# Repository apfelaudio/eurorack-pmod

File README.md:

# Eurorack PMOD

**Eurorack PMOD** is a [certified open hardware](https://certification.oshwa.org/de000135.html) Eurorack module that plugs directly into many FPGA boards, which makes it easy to combine the world of FPGAs and [hardware electronic music synthesis](https://en.wikipedia.org/wiki/Eurorack). The latest (R3.3) hardware looks like this:

## How does it work? ([tutorial video](https://youtu.be/TcqFej9GK8U))
- Plug eurorack-pmod into an FPGA development board of your choice. Here is a list of [boards already supported by the examples](gateware/boards).
- Get started with some [example DSP cores](gateware/cores). Examples include calibration, sampling, effects, synthesis sources and so on. The design files can be synthesized to a bitstream using Yosys' [oss-cad-suite](https://github.com/YosysHQ/oss-cad-suite-build).

## :notes: Project Showcase :sparkles:

- **[FPGA-based neural-net waveshaper](https://matpalm.com/blog/wavenet_on_fpga/)** - (from [matpalm@](https://github.com/matpalm))
- **[Teensy 4.x I2S TDM w/ Eurorack PMOD](https://github.com/Lytrix/Teensy4-i2s-TDM)** - (from [lytrix@](https://github.com/Lytrix))
- **[8-channel USB2 soundcard](https://github.com/apfaudio/eurorack-pmod-usb-soundcard)** - mostly in Amaranth.
- **[Daisy Seed TDM for Eurorack PMOD](https://github.com/heartwerker/daisy_seed_tdm_eurorack_pmod)** - (from [heartwerker@](https://github.com/heartwerker))
- **[`apu_chord` core](https://github.com/proppy/eurorack-pmod/tree/apu_chord)** - (from [proppy@](https://github.com/proppy))
- **[Real-time DSP with Rust on LiteX](https://github.com/apfaudio/eurorack-pmod-litex)** - mostly in Rust/Migen.

# R3.3 hardware details

- 3HP module compatible with modular synthesizer systems.
    - Module depth is 35mm with both ribbon cables attached.
- [PMOD](https://en.wikipedia.org/wiki/Pmod_Interface) connector compatible with many FPGA development boards.
- 8 (4 in + 4 out) DC-coupled audio channels, 192KHz / 32bit sampling supported.
- PWM-controlled, user-programmable red/green LEDs on each output channel.
- Jack insertion detection on input & output jacks.
- Calibration EEPROM for unique ID and storing calibration data.
- [new!] Touch and proximity sensing on all unused jacks as an extra input method.
    - See the `gateware/cores/touch_cv.sv` core for an example of how to use this.

**Compared to R3.1, the changes across R3.2 and R3.3 [are summarized here](https://github.com/apfaudio/eurorack-pmod/issues/50)**

[Want one?](#manufacturing). More photos can be found [below](#photos).

## Included examples
This repository contains a bunch of example DSP cores which are continuously being updated:
- `gateware/cores/pitch_shift.sv` - Pitch shifter
- `gateware/cores/filter.sv` - Filter (low pass + resonance)
- `gateware/cores/touch_cv.sv` - Touch sensing to CV converter
- `gateware/cores/clkdiv.sv` - Clock divider
- `gateware/cores/sampler.sv` - .wav sampler
- `gateware/cores/seqswitch.sv` - Sequential routing switch
- `gateware/cores/digital_echo.sv` - Echo / delay effect
- `gateware/cores/vca.sv` - VCA (voltage controlled amplifier)
- `gateware/cores/vco.sv` - VCO (voltage controlled oscillator)
- `gateware/cores/bitcrush.sv` - Bitcrusher

These examples can all run out of the box on the development boards listed below.

## Choosing an FPGA development board
An FPGA development board itself is NOT included! Essentially anything iCE40 or ECP5 based that has a PMOD connector will support the open-source tools and the examples in this project. Just make sure you have enough LUTS, >3K is enough to do interesting things.

The following development boards have been tested with `eurorack-pmod` and are supported by the examples in the github repository
- iCEbreaker (iCE40 based)
- [iCESugar](https://github.com/wuxx/icesugar) (iCE40 based, iCE40UP5K version)
- ECPIX-5 (ECP5 based)
- Colorlight i5 (ECP5 based)
- Colorlight i9 (ECP5 based)
- pico-ice from TinyVision (iCE40 based)
- CCGM1A1 Gatemate EVB from CologneChip - [**experimental!** see here](gateware/boards/gatemate_evb/README.md)

## PMOD Pinout

The PMOD pinout is on the silkscreen on the back side of the board. Details are below. Note that Pin 1 is the SQUARE pad.

1) SDI (AK4619VN SDIN1)
2) SCL (I2C SCL for AK4619VN CODEC, EEPROM, LED + JACK IO expanders)
3) SDO (AK4619VN SDOUT1)
4) SDA (I2C SDA)
5) LRCK (CODEC clock line)
6) PDN (CODEC power down, also connected to LED output enable and JACK reset line -- HIGH means everything is on)
7) BICK (CODEC clock line)
8) MCLK (CODEC clock line)
9) GND
10) GND
11) 3V3 IN
12) 3V3 IN

## Getting Started

I have tested builds on Linux, Mac and Windows (under MSYS2). All are tested in CI.

0. Install the [OSS FPGA CAD flow](https://github.com/yosyshq/oss-cad-suite-build).
    - You may be able to get yosys / verilator from other package managers but I recommend using the [releases from YosysHQ](https://github.com/yosyshq/oss-cad-suite-build) so you're using the same binaries that CI is using.
    - On Linux, once the YosysHQ suite is installed and in PATH, you should be able to just use `make` in the gateware directory.
    - On Windows, CI is using MSYS2 with MINGW64 shell. Install MSYS2, MINGW64, extract the oss-cad-suite from YosysHQ and add it to PATH. Then you should be able to use `make` in the gateware directory.
    - Note: The gateware is automatically built and tested in CI, so for either platform it may be helpful to look at [`.github/workflows/main.yml`](.github/workflows/main.yml).

1. Build or obtain `eurorack-pmod` hardware and connect it to your FPGA development board using a ribbon cable or similar. (Double check that the pin mappings are correct, some ribbon cables will swap them on you! Default pinmaps are for the ribbon cables I shipped with hardware, you need to flip the pinmaps for a direct connection PMOD -> FPGA)
2. Try some of the examples. From the `gateware` directory, type `make` to see valid commands. By default if you do not select a CORE it will compile a bitstream with the 'mirror' core, which just sends inputs to outputs. Note, you'll need to run `git submodule update --init --recursive` from the repo root after checkout.
2. Calibrate your hardware using the process described in [`gateware/cal/cal.py`](gateware/cal/cal.py). Use this to create your own `gateware/cal/cal_mem.hex` to compensate for any DC biases in the ADCs/DACs. (this step is only necessary if you need sub-50mV accuracy on your inputs/outputs, which is the case if you are tuning oscillators, not so much if you are creating rhythm pulses.

# Project structure
The project is split into 2 directories, [`hardware`](hardware) for the PCB/panel and [`gateware`](gateware) for the FPGA source. Some interesting directories:
- [`gateware/cores`](gateware/cores): example user core implementations (i.e sequential switch, bitcrusher, filter, vco, vca, sampler etc).
- [`gateware/top.sv`](gateware/top.sv): top-level gateware with defines for selecting features.
- [`gateware/cal/cal.py`](gateware/cal/cal.py): tool used to calibrate the hardware after assembly, generating calibration memory.
- [`gateware/drivers`](gateware/drivers): driver for CODEC and I2C devices used on this board.
- [`hardware/eurorack-pmod-r3`](hardware/eurorack-pmod-r3): KiCAD design files for PCB and front panel.
- [`hardware/fab`](hardware/fab): gerber files and BOM for manufacturing the hardware.

# Manufacturing

# R3.1 Hardware (no longer manufactured)

The above README focuses on R3.3, which is currently being manufactured.

Revision R3.1 was sold out in 2023. It's no longer manufactured, however this repository still supports it if you use the `HW_REV=HW_R31` flag when building. I left some of the old photos here in case they are useful.

From the gateware perspective, there is almost no difference between R3.1 and R3.3 and so any cores should be compatible with both (unless they use new features of R3.3 e.g. touch sensitive jacks).

## R3.1 boards

## R3.1 hardware details

## R3.1 technical

- 3HP module compatible with modular synthesizer systems.
    - Module depth is 47mm with both ribbon cables attached
    - This fits nicely in e.g. a 4MS POD 48X (pictured below).
- PMOD connector compatible with most FPGA development boards.
- 8 (4 in + 4 out) DC-coupled audio channels, 192KHz / 32bit sampling supported.
- PWM-controlled, user-programmable red/green LEDs on each output channel.
- Jack insertion detection on input & output jacks.
- Calibration EEPROM for unique ID and storing calibration data.
- I/O is about +/- 8V capable, wider is possible with a resistor change.

## Known limitations
- Moved to github issues

# Photos

## `eurorack-pmod` R3.1 connected to iCEBreaker

# License

Hardware and gateware are released under the CERN Open-Hardware License V2 `CERN-OHL-S`, mirrored in the LICENSE text in this repository.

If you wish to license parts of this design in a commercial product without a reciprocal open-source license, or you have a ground-breaking idea for a module we could work on together, feel free to contact me directly. See sebholzapfel.com.

*Copyright (C) 2022-2024 Sebastian Holzapfel*

The above LICENSE and copyright notice does NOT apply to imported artifacts in this repository (i.e datasheets, third-party footprints).

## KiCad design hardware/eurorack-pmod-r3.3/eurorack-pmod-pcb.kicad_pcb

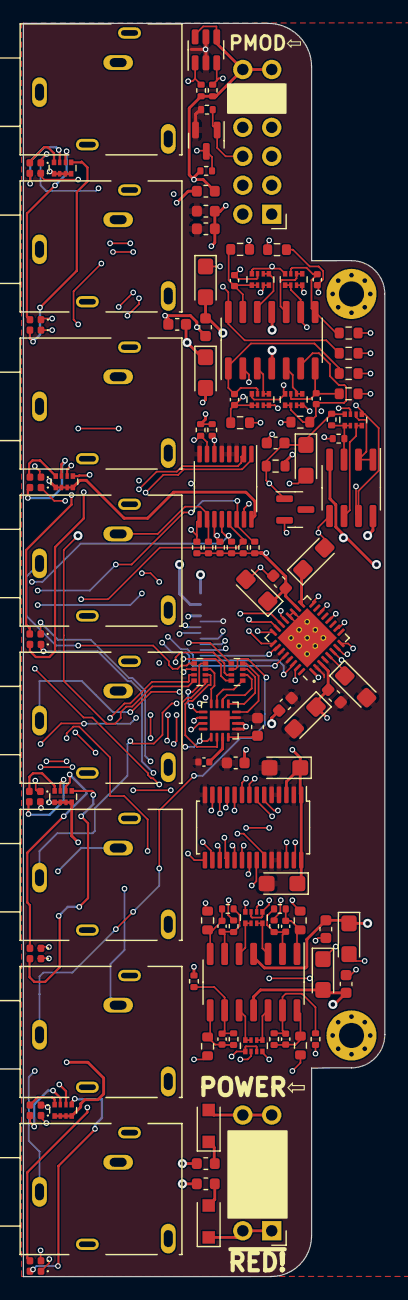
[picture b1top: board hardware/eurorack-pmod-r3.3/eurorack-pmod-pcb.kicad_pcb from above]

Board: 4 copper layers, 31.7 x 110.0 mm, 122 parts (1 on the bottom side), 124 nets.

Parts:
C2, C6, C8, C13, C14, C15, C17, C27, C29, C31: 100nF; C_0603_1608Metric
C3, C10, C16, C28: 100.0uF; CP_EIA-3216-10_Kemet-I
C4, C5, C9, C11, C26: 22.0uF; CP_EIA-3216-10_Kemet-I
C7, C12: 2.2uF; CP_EIA-3216-10_Kemet-I
C18, C19, C20, C21: 220pF; C_0402_1005Metric
C22, C23, C24, C25: 56p; C_0402_1005Metric
C30: 2.2nF; C_0402_1005Metric
D1, D2: 1N4007FL; D_SOD-123F
D3, D5, D7, D9, D11, D13, D15, D17: LED 0402 GREEN; LED_0402_1005Metric
D4, D6, D8, D10, D12, D14, D16, D18: LED 0402 RED; LED_0402_1005Metric
J1: CONN 2x5 P=2.54mm; PinHeader_2x05_P2.54mm_Horizontal
J2: CONN 2x6 P=2.54mm; PinHeader_2x06_P2.54mm_Horizontal
J3: Conn_01x14_Socket; FFC_0.5-14P_CTXJ-H2.0_1
J4, J5, J6, J7, J8, J9, J10, J11: AUDIO JACK PJ-324M0; pj324m
L1, L2, L3, L4, L5: FERRITE; L_0603_1608Metric
Q1: 2N7002E; SOT-23
R1, R2, R3, R4, R5, R8, R11, R14, R17, R20, R21, R24, R25, R28, R29, R32: 4K7; R_0402_1005Metric
R6, R9, R12, R15: 100K; R_0603_1608Metric
R7, R10, R13, R16, R18, R22, R26, R30: 1K; R_0603_1608Metric
R19, R23, R27, R31: 56K; R_0402_1005Metric
R33: 330R; R_0603_1608Metric
R42: X.X; R_0402_1005Metric
R43: 402K; R_0402_1005Metric
RN1, RN2, RN3, RN4: 14.3K; R_Array_Convex_4x0402
RN5, RN6, RN7: 100K; R_Array_Convex_4x0402
RN8, RN9, RN10, RN11: 120R; R_Array_Convex_4x0402
RN12, RN13: 560R; R_Array_Convex_4x0402
U1: AK4619VN AUDIO CODEC; QFN-32-1EP_5x5mm_P0.5mm_EP3.7x3.7mm_ThermalVias
U2, U3: TL074 OP AMP; SOIC-14_3.9x8.7mm_P1.27mm
U4: PCA9557PW IO EXPANDER; TSSOP-16_4.4x5mm_P0.65mm
U5: 24AA025UIDT EEPROM; SOT-23-6
U6: CY8CMBR3108; QFN-16-1EP_3x3mm_P0.5mm_EP1.75x1.75mm
U8: LM4040DBZ-3 VREF; SOT-23
U9: TL072 OP AMP; SOIC-8_3.9x4.9mm_P1.27mm
U10: PCA9635 LED DRIVER; TSSOP-28_4.4x9.7mm_P0.65mm

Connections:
+3.3VA: C10.1, C14.1, L4.1, R5.2, R8.2, R11.2, R14.2, R17.2, R21.2, R25.2, R29.2, R33.2, U1.18 (AVDD)
+12V: C5.1, C8.1, C11.1, C15.1, J3.3, L1.1, U2.4 (V+), U3.4 (V+), U9.8 (V+)
-12V: C4.2, C6.2, C9.2, C13.2, J3.1, L2.1, U2.11 (V-), U3.11 (V-), U9.4 (V-)
/-VCOM: RN1.8 (R1.2), RN2.8 (R1.2), RN3.8 (R1.2), RN4.8 (R1.2), RN5.1 (R1.1), RN5.3 (R3.1), RN6.1 (R1.1), RN6.3 (R3.1), RN7.5 (R4.2), U9.7
/BICK: J2.7, J3.10, U1.7 (BICK)
/CAP_SENSE_IN1: J4.G, RN12.8 (R1.2)
/CAP_SENSE_IN2: J5.G, RN12.7 (R2.2)
/CAP_SENSE_IN3: J6.G, RN12.6 (R3.2)
/CAP_SENSE_IN4: J7.G, RN12.5 (R4.2)
/CAP_SENSE_OUT1: J8.G, RN13.8 (R1.2)
/CAP_SENSE_OUT2: J9.G, RN13.7 (R2.2)
/CAP_SENSE_OUT3: J10.G, RN13.6 (R3.2)
/CAP_SENSE_OUT4: J11.G, RN13.5 (R4.2)
/JACK_DETECT_IN1: J4.SN, R5.1, U4.6 (IO0)
/JACK_DETECT_IN2: J5.SN, R8.1, U4.7 (IO1)
/JACK_DETECT_IN3: J6.SN, R11.1, U4.9 (IO2)
/JACK_DETECT_IN4: J7.SN, R14.1, U4.10 (IO3)
/JACK_DETECT_OUT1: J8.SN, R17.1, U4.11 (IO4)
/JACK_DETECT_OUT2: J9.SN, R21.1, U4.12 (IO5)
/JACK_DETECT_OUT3: J10.SN, R25.1, U4.13 (IO6)
/JACK_DETECT_OUT4: J11.SN, R29.1, U4.14 (IO7)
/LRCK: J2.5, J3.9, U1.6 (LRCK)
/MCLK: J2.8, J3.11, U1.8 (MCLK)
/PDN: J2.6, J3.12, Q1.1 (G), R4.2, U1.26 (PDN), U4.15 (~RESET)
/SCL: J2.2, J3.14, R1.1, U1.28 (SCL/SCLK), U4.1 (SCL), U5.1 (SCL), U6.15 (SCL), U10.26 (SCL)
/SDA: J2.4, J3.13, R2.1, U1.30 (SDA/SO), U4.2 (SDA), U5.3 (SDA), U6.14 (SDA), U10.27 (SDA)
/SDIN1: J2.1, J3.7, U1.1 (SDIN1)
/SDOUT1: J2.3, J3.8, U1.31 (SDOUT1)
/dual_mono_inputs1/IN1_3V: R7.2, U1.16 (IN1P/AIN1L/AIN3L)
/dual_mono_inputs1/IN2_3V: R10.2, U1.14 (IN2P/AIN1R/AIN3R)
/dual_mono_inputs2/IN1_3V: R13.2, U1.12 (IN3P/AIN4L/AIN6L)
/dual_mono_inputs2/IN2_3V: R16.2, U1.10 (IN4P/AIN4R/AIN6R)
/dual_mono_outputs1/OUT1: RN5.2 (R2.1), U1.22 (AOUT1L)
/dual_mono_outputs1/OUT2: RN5.4 (R4.1), U1.23 (AOUT1R)
/dual_mono_outputs2/OUT1: RN6.2 (R2.1), U1.24 (AOUT2L)
/dual_mono_outputs2/OUT2: RN6.4 (R4.1), U1.25 (AOUT2R)
/vref/+3V0_AREF: C26.1, C27.1, R33.1, R43.2, RN7.8 (R1.2), U1.21 (VREFH), U8.1 (K)
/~PDN: Q1.3 (D), R3.1, U10.23 (~OE)
GND: C4.1, C5.2, C6.1, C8.2, C9.1, C10.2, C11.2, C12.2, C13.1, C14.2, C15.2, C26.2, C27.2, J1.3, J1.4, J1.5, J1.6, J1.7, J1.8, J3.4, J4.S, J4.TN, J5.S, J5.TN, J6.S, J6.TN, J7.S, J7.TN, J8.S, J8.TN, J9.S, J9.TN, J10.S, J10.TN, J11.S, J11.TN, L3.1, L5.1, R20.1, R24.1, R28.1, R32.1, R42.1, RN1.3 (R3.1), RN1.4 (R4.1), RN2.3 (R3.1), RN2.4 (R4.1), RN3.3 (R3.1), RN3.4 (R4.1), RN4.3 (R3.1), RN4.4 (R4.1), RN7.7 (R2.2), U1.19 (VSS1), U1.20 (VREFL), U1.33 (PAD), U8.2 (A), U9.5 (+)
GNDD: C2.2, C3.2, C7.2, C16.2, C17.2, C28.2, C29.2, C30.2, C31.2, J2.9, J2.10, J3.6, L3.2, L5.2, Q1.2 (S), R4.1, U1.2 (SDIN2), U1.4 (VSS2), U1.27 (CAD/~CS), U1.29 (SI), U4.3 (A0), U4.4 (A1), U4.5 (A2), U4.8 (VSS), U5.2 (V_{SS}), U5.5 (WP), U6.7 (VSS), U6.17 (EP), U10.2 (A1), U10.4 (A3), U10.5 (A4), U10.14 (VSS), U10.24 (A5), U10.25 (A6)
unnamed: C22.2, R18.1, R19.1, U2.1
unnamed: C23.2, R22.1, R23.1, U2.7
unnamed: C24.2, R26.1, R27.1, U2.8
unnamed: C25.2, R30.1, R31.1, U2.14
unnamed: D1.2 (A), J1.9, J1.10
unnamed: D1.1 (K), L1.2
unnamed: D2.2 (A), L2.2
unnamed: D2.1 (K), J1.1, J1.2
unnamed: D3.2 (A), RN8.8 (R1.2)
unnamed: D3.1 (K), U10.6 (LED0)
unnamed: D4.2 (A), RN8.7 (R2.2)
unnamed: D4.1 (K), U10.7 (LED1)
unnamed: D5.2 (A), RN8.6 (R3.2)
unnamed: D5.1 (K), U10.8 (LED2)
unnamed: D6.2 (A), RN8.5 (R4.2)
unnamed: D6.1 (K), U10.9 (LED3)
unnamed: D7.2 (A), RN9.8 (R1.2)
unnamed: D7.1 (K), U10.10 (LED4)
unnamed: D8.2 (A), RN9.7 (R2.2)
unnamed: D8.1 (K), U10.11 (LED5)
unnamed: D9.2 (A), RN9.6 (R3.2)
unnamed: D9.1 (K), U10.12 (LED6)
unnamed: D10.2 (A), RN9.5 (R4.2)
unnamed: D10.1 (K), U10.13 (LED7)
unnamed: D11.2 (A), RN10.8 (R1.2)
unnamed: D11.1 (K), U10.15 (LED8)
unnamed: D12.2 (A), RN10.7 (R2.2)
unnamed: D12.1 (K), U10.16 (LED9)
unnamed: D13.2 (A), RN10.6 (R3.2)
unnamed: D13.1 (K), U10.17 (LED10)
unnamed: D14.2 (A), RN10.5 (R4.2)
unnamed: D14.1 (K), U10.18 (LED11)
unnamed: D15.2 (A), RN11.8 (R1.2)
unnamed: D15.1 (K), U10.19 (LED12)
unnamed: D16.2 (A), RN11.7 (R2.2)
unnamed: D16.1 (K), U10.20 (LED13)
unnamed: D17.2 (A), RN11.6 (R3.2)
unnamed: D17.1 (K), U10.21 (LED14)
unnamed: D18.2 (A), RN11.5 (R4.2)
unnamed: D18.1 (K), U10.22 (LED15)
unnamed: J4.T, R6.1
unnamed: J5.T, R9.1
unnamed: J6.T, R12.1
unnamed: J7.T, R15.1
unnamed: J8.T, R18.2
unnamed: J9.T, R22.2
unnamed: J10.T, R26.2
unnamed: J11.T, R30.2
unnamed: C18.1, R6.2, RN1.1 (R1.1), RN1.2 (R2.1), U3.2 (-)
unnamed: C18.2, R7.1, RN1.7 (R2.2), U3.1
unnamed: RN1.5 (R4.2), RN1.6 (R3.2), U3.3 (+)
unnamed: C19.1, R9.2, RN2.1 (R1.1), RN2.2 (R2.1), U3.6 (-)
unnamed: C19.2, R10.1, RN2.7 (R2.2), U3.7
unnamed: RN2.5 (R4.2), RN2.6 (R3.2), U3.5 (+)
unnamed: C20.1, R12.2, RN3.1 (R1.1), RN3.2 (R2.1), U3.9 (-)
unnamed: C20.2, R13.1, RN3.7 (R2.2), U3.8
unnamed: RN3.5 (R4.2), RN3.6 (R3.2), U3.10 (+)
unnamed: C21.1, R15.2, RN4.1 (R1.1), RN4.2 (R2.1), U3.13 (-)
unnamed: C21.2, R16.1, RN4.7 (R2.2), U3.14
unnamed: RN4.5 (R4.2), RN4.6 (R3.2), U3.12 (+)
unnamed: RN5.7 (R2.2), RN5.8 (R1.2), U2.3 (+)
unnamed: RN5.5 (R4.2), RN5.6 (R3.2), U2.5 (+)
unnamed: RN6.7 (R2.2), RN6.8 (R1.2), U2.10 (+)
unnamed: RN6.5 (R4.2), RN6.6 (R3.2), U2.12 (+)
unnamed: R42.2, R43.1, RN7.1 (R1.1), RN7.2 (R2.1), U9.3 (+)
unnamed: RN7.3 (R3.1), RN7.4 (R4.1), U9.6 (-)
unnamed: RN7.6 (R3.2), U9.1, U9.2 (-)
unnamed: RN12.1 (R1.1), U6.1 (CS0)
unnamed: RN12.2 (R2.1), U6.2 (CS1)
unnamed: RN12.3 (R3.1), U6.12 (CS2)
unnamed: RN12.4 (R4.1), U6.13 (CS3)
unnamed: RN13.1 (R1.1), U6.11 (CS7)
unnamed: RN13.2 (R2.1), U6.10 (CS6)
unnamed: RN13.3 (R3.1), U6.9 (CS5)
unnamed: RN13.4 (R4.1), U6.8 (CS4)
unnamed: C7.1, U1.5 (AVDRV)
unnamed: C12.1, U1.17 (VCOM)
unnamed: C22.1, R19.2, R20.2, U2.2 (-)
unnamed: C23.1, R23.2, R24.2, U2.6 (-)
unnamed: C24.1, R27.2, R28.2, U2.9 (-)
unnamed: C25.1, R31.2, R32.2, U2.13 (-)
unnamed: C30.1, U6.3 (CMOD)
unnamed: C31.1, U6.4 (VCC)
VDD: C2.1, C3.1, C16.1, C17.1, C28.1, C29.1, J2.11, J2.12, J3.5, L4.2, R1.2, R2.2, R3.2, RN8.1 (R1.1), RN8.2 (R2.1), RN8.3 (R3.1), RN8.4 (R4.1), RN9.1 (R1.1), RN9.2 (R2.1), RN9.3 (R3.1), RN9.4 (R4.1), RN10.1 (R1.1), RN10.2 (R2.1), RN10.3 (R3.1), RN10.4 (R4.1), RN11.1 (R1.1), RN11.2 (R2.1), RN11.3 (R3.1), RN11.4 (R4.1), U1.3 (TVDD), U4.16 (VDD), U5.4 (V_{CC}), U6.5 (VDDIO), U6.6 (VDD), U10.1 (A0), U10.3 (A2), U10.28 (VDD)

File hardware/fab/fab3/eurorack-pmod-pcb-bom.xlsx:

Comment | Designator | Footprint | LCSC Part # | Manufacturer Part #
10.0uF | C1, C3, C8, C10, C13, C16, C26, C28, | Capacitor_Tantalum_SMD:CP_EIA-3216-10_Kemet-I | C110055 | T491A106K016AT
100nF | C2, C4, C9, C11, C14, C17, C27, C29, | Capacitor_SMD:C_0603_1608Metric | C338036 | C1608X7R1E104KT000N
47uF | C5, C6, C15, | Capacitor_SMD:CP_Elec_6.3x5.4 | C88735 | 25SEV47M6.3X5.5
2.2uF | C7, C12, | Capacitor_Tantalum_SMD:CP_EIA-3216-10_Kemet-I | C1953682 | T491A225K020AT
220pF | C18, C19, C20, C21, | Capacitor_SMD:C_0402_1005Metric | C107025 | CC0402KRX7R9BB221
56p | C22, C23, C24, C25, | Capacitor_SMD:C_0402_1005Metric | C526981 | CC0402FRNPO9BN560
1N4007FL | D1, D2, | Diode_SMD:D_SOD-123F | C2840959 | 1N4007FL
LED 0402 YELLOW | D3, D5, D7, D9, D11, D13, D15, D17, | LED_SMD:LED_0402_1005Metric | C2846629 | SML-P12WTT86R
LED 0402 RED | D4, D6, D8, D10, D12, D14, D16, D18, | LED_SMD:LED_0402_1005Metric | C123072 | SML-P12UTT86R
[NO POP] CONN 2x5 P=2.54mm | J1, | Connector_PinHeader_2.54mm:PinHeader_2x05_P2.54mm_Vertical
[NO POP] CONN 2x6 P=2.54mm | J2, | Connector_PinHeader_2.54mm:PinHeader_2x06_P2.54mm_Vertical
AUDIO JACK PJ-324M0 | J4, J5, J6, J7, J8, J9, J10, J11, | AudioJacksFixed:pj324m | C2884986 | PJ-324M0
FERRITE | L1, L2, L3, L4, L5, L6, | Inductor_SMD:L_0603_1608Metric | C88986 | BLM18RK102SN1D
2N7002E | Q1, | Package_TO_SOT_SMD:SOT-23 | C71533 | 2N7002ET1G
4K7 | R1, R2, R3, R4, R5, R8, R11, R14, R17, R20, R21, R24, R25, R28, R29, R32, | Resistor_SMD:R_0402_1005Metric | C105871 | RC0402FR-074K7L
100K | R6, R9, R12, R15, | Resistor_SMD:R_0603_1608Metric | C14675 | RC0603FR-07100KL
1K | R7, R10, R13, R16, R18, R22, R26, R30, | Resistor_SMD:R_0603_1608Metric | C22548 | RC0603FR-071KL
56K | R19, R23, R27, R31, | Resistor_SMD:R_0402_1005Metric | C114756 | RC0402FR-0756KL
330R | R33, | Resistor_SMD:R_0603_1608Metric | C105881 | RC0603FR-07330RL
10K | RN1, RN2, RN3, RN4, | Resistor_SMD:R_Array_Convex_4x0402 | C136853 | YC124-FR-0710KL
100K | RN5, RN6, RN7, | Resistor_SMD:R_Array_Convex_4x0402 | C326786 | YC124-FR-07100KL
100R | RN8, RN9, RN10, RN11, | Resistor_SMD:R_Array_Convex_4x0402 | C326873 | YC124-JR-07100RL
AK4619VN AUDIO CODEC | U1, | Package_DFN_QFN:QFN-32-1EP_5x5mm_P0.5mm_EP3.7x3.7mm_ThermalVias |  | AK4619VN
TL074 OP AMP | U2, U3, | Package_SO:SOIC-14_3.9x8.7mm_P1.27mm | C6963 | TL074CDT
PCA9557PW IO EXPANDER | U4, | Package_SO:TSSOP-16_4.4x5mm_P0.65mm | C141380 | PCA9557PW,118
24AA025UIDT EEPROM | U5, | Package_TO_SOT_SMD:SOT-23-5 | C2061498 | 24AA025UIDT-I/OT
LM4040DBZ-3 VREF | U8, | Package_TO_SOT_SMD:SOT-23 | C139380 | LM4040BIM3-3.0/NOPB
TL072 OP AMP | U9, | Package_SO:SOIC-8_3.9x4.9mm_P1.27mm | C6961 | TL072CDT
PCA9635 LED DRIVER | U10, | Package_SO:TSSOP-28_4.4x9.7mm_P0.65mm | C110795 | PCA9635PW,118

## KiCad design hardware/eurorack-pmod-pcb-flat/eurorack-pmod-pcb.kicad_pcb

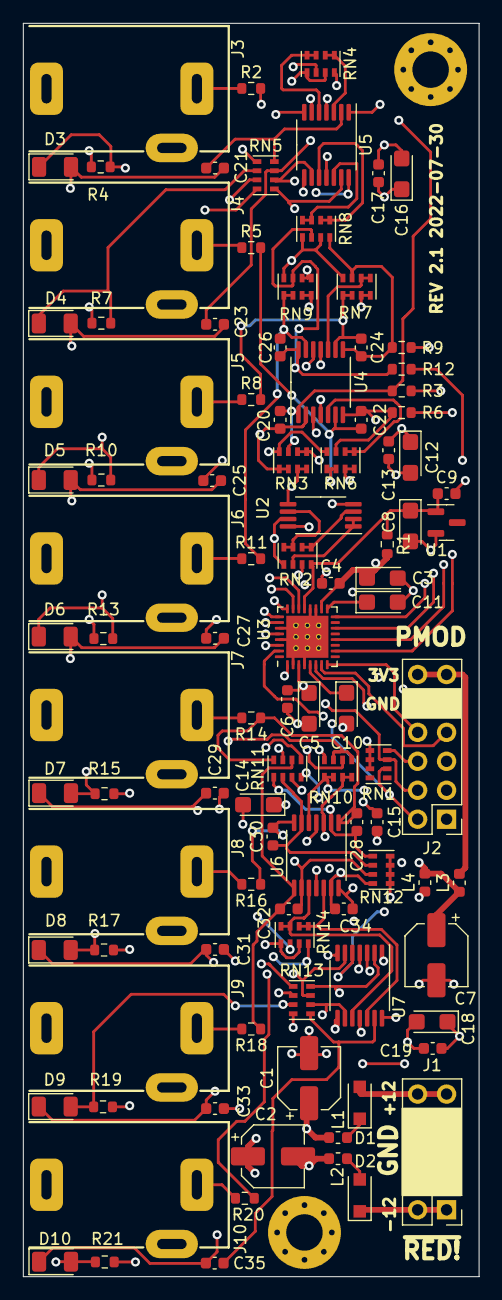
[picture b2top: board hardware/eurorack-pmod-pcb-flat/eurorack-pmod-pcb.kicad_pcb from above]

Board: 4 copper layers, 40.0 x 110.0 mm, 101 parts (0 on the bottom side), 93 nets.

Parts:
C1, C2, C7: 47u; CP_Elec_5x5.3
C3, C5, C8, C12, C14, C16, C18: 10u; CP_EIA-3216-10_Kemet-I
C4, C6, C9, C13, C15, C17, C19: 100n; C_0603_1608Metric
C10, C11: 2u2; CP_EIA-3216-10_Kemet-I
C20, C21, C22, C23, C24, C25, C26, C27, C29, C31, C33, C35: 220p; C_0603_1608Metric
C28, C30, C32, C34: 56p; C_0603_1608Metric
D1, D2: 1N4007FL; D_SOD-123F
D3, D4, D5, D6, D7, D8, D9, D10: LED_AN; LED_1206_3216Metric
J1: EURORACK_PWR; PinHeader_2x05_P2.54mm_Vertical
J2: PMOD; PinHeader_2x06_P2.54mm_Vertical
J3, J4, J5, J6, J7, J8, J9, J10: PJ398SM; Jack_3.5mm_QingPu_WQP-PJ302M_Horizontal
L1, L2, L3, L4: Ferrite; L_0603_1608Metric
R1: 330R; R_0603_1608Metric
R2, R5, R8, R11: 100K; R_0603_1608Metric
R3, R6, R9, R12, R14, R16, R18, R20: 1K; R_0603_1608Metric
R4, R7, R10, R13, R15, R17, R19, R21: 100R; R_0603_1608Metric
RN1, RN12: 4K7; R_Cat16-4
RN2, RN4, RN8, RN10, RN14: 100K; R_Cat16-4
RN3, RN5, RN6, RN7, RN9, RN13: 15K; R_Cat16-4
RN11: 56K; R_Cat16-4
U1: LM4040DBZ-3; SOT-23
U2: TL072; TSSOP-8_4.4x3mm_P0.65mm
U3: AK4619VN; QFN-32-1EP_5x5mm_P0.5mm_EP3.7x3.7mm_ThermalVias
U4, U5, U6, U7: TL074; TSSOP-14_4.4x5mm_P0.65mm

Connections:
+3.3VA: C3.1, C4.1, L4.1, R1.2, U3.18 (AVDD)
+12V: C1.1, C12.1, C13.1, C14.1, C15.1, L1.1, U2.8 (V+), U4.4 (V+), U5.4 (V+), U6.4 (V+), U7.4 (V+)
-12V: C2.2, C16.2, C17.2, C18.2, C19.2, L2.1, U2.4 (V-), U4.11 (V-), U5.11 (V-), U6.11 (V-), U7.11 (V-)
/-VCOM: RN2.5 (R4.2), RN3.8 (R1.2), RN4.5 (R4.2), RN4.7 (R2.2), RN6.8 (R1.2), RN7.8 (R1.2), RN8.5 (R4.2), RN8.7 (R2.2), RN9.8 (R1.2), RN10.1 (R1.1), RN10.3 (R3.1), RN14.1 (R1.1), RN14.3 (R3.1), U2.7
/BICK: J2.7, U3.7 (BICK)
/LRCK: J2.5, U3.6 (LRCK)
/MCLK: J2.8, U3.8 (MCLK)
/PDN: J2.6, RN1.4 (R4.1), U3.26 (PDN)
/SCL: J2.2, RN1.2 (R2.1), U3.28 (SCL/SCLK)
/SDA: J2.4, RN1.3 (R3.1), U3.30 (SDA/SO)
/SDIN1: J2.1, U3.1 (SDIN1)
/SDOUT1: J2.3, U3.31 (SDOUT1)
/VREFH: C8.1, C9.1, R1.1, RN2.8 (R1.2), U1.1 (K), U3.21 (VREFH)
/dual_mono_inputs1/IN1_3V: R3.2, U3.16 (IN1P/AIN1L/AIN3L)
/dual_mono_inputs1/IN2_3V: R6.2, U3.14 (IN2P/AIN1R/AIN3R)
/dual_mono_inputs2/IN1_3V: R9.2, U3.12 (IN3P/AIN4L/AIN6L)
/dual_mono_inputs2/IN2_3V: R12.2, U3.10 (IN4P/AIN4R/AIN6R)
/dual_mono_outputs1/OUT1: RN10.2 (R2.1), U3.22 (AOUT1L)
/dual_mono_outputs1/OUT2: RN10.4 (R4.1), U3.23 (AOUT1R)
/dual_mono_outputs2/OUT1: RN14.2 (R2.1), U3.24 (AOUT2L)
/dual_mono_outputs2/OUT2: RN14.4 (R4.1), U3.25 (AOUT2R)
GND: C1.2, C2.1, C3.2, C4.2, C5.2, C6.2, C7.2, C8.2, C9.2, C10.2, C11.2, C12.2, C13.2, C14.2, C15.2, C16.1, C17.1, C18.1, C19.1, J1.3, J1.4, J1.5, J1.6, J1.7, J1.8, J2.9, J2.10, J3.S, J3.TN, J4.S, J4.TN, J5.S, J5.TN, J6.S, J6.TN, J7.S, J8.S, J9.S, J10.S, R4.1, R7.1, R10.1, R13.1, R15.1, R17.1, R19.1, R21.1, RN2.7 (R2.2), RN3.3 (R3.1), RN3.4 (R4.1), RN6.3 (R3.1), RN6.4 (R4.1), RN7.3 (R3.1), RN7.4 (R4.1), RN9.3 (R3.1), RN9.4 (R4.1), RN12.5 (R4.2), RN12.6 (R3.2), RN12.7 (R2.2), RN12.8 (R1.2), U1.2 (A), U2.5 (+), U3.2 (SDIN2), U3.4 (VSS2), U3.19 (VSS1), U3.20 (VREFL), U3.27 (CAD/~CS), U3.29 (SI), U3.33 (PAD)
unnamed: C10.1, U3.5 (AVDRV)
unnamed: C11.1, U3.17 (VCOM)
unnamed: C20.1, R2.2, RN3.1 (R1.1), RN3.2 (R2.1), U4.2 (-)
unnamed: C20.2, R3.1, RN3.7 (R2.2), RN4.8 (R1.2), U4.1
unnamed: C21.1, RN5.8 (R1.2), U5.2 (-)
unnamed: C21.2, D3.2 (AK), U5.1
unnamed: C22.1, R5.2, RN6.1 (R1.1), RN6.2 (R2.1), U4.6 (-)
unnamed: C22.2, R6.1, RN4.6 (R3.2), RN6.7 (R2.2), U4.7
unnamed: C23.1, RN5.7 (R2.2), U5.6 (-)
unnamed: C23.2, D4.2 (AK), U5.7
unnamed: C24.1, R8.2, RN7.1 (R1.1), RN7.2 (R2.1), U4.9 (-)
unnamed: C24.2, R9.1, RN7.7 (R2.2), RN8.8 (R1.2), U4.8
unnamed: C25.1, RN5.6 (R3.2), U5.9 (-)
unnamed: C25.2, D5.2 (AK), U5.8
unnamed: C26.1, R11.2, RN9.1 (R1.1), RN9.2 (R2.1), U4.13 (-)
unnamed: C26.2, R12.1, RN8.6 (R3.2), RN9.7 (R2.2), U4.14
unnamed: C27.1, RN5.5 (R4.2), U5.13 (-)
unnamed: C27.2, D6.2 (AK), U5.14
unnamed: C28.1, RN11.1 (R1.1), RN12.1 (R1.1), U6.2 (-)
unnamed: C28.2, R14.1, RN11.8 (R1.2), U6.1
unnamed: C29.1, RN13.8 (R1.2), U7.2 (-)
unnamed: C29.2, D7.1 (KA), U7.1
unnamed: C30.1, RN11.2 (R2.1), RN12.2 (R2.1), U6.6 (-)
unnamed: C30.2, R16.1, RN11.7 (R2.2), U6.7
unnamed: C31.1, RN13.7 (R2.2), U7.6 (-)
unnamed: C31.2, D8.1 (KA), U7.7
unnamed: C32.1, RN11.3 (R3.1), RN12.3 (R3.1), U6.9 (-)
unnamed: C32.2, R18.1, RN11.6 (R3.2), U6.8
unnamed: C33.1, RN13.6 (R3.2), U7.9 (-)
unnamed: C33.2, D9.1 (KA), U7.8
unnamed: C34.1, RN11.4 (R4.1), RN12.4 (R4.1), U6.13 (-)
unnamed: C34.2, R20.1, RN11.5 (R4.2), U6.14
unnamed: C35.1, RN13.5 (R4.2), U7.13 (-)
unnamed: C35.2, D10.1 (KA), U7.14
unnamed: D1.1 (K), L1.2
unnamed: D1.2 (A), J1.9, J1.10
unnamed: D2.1 (K), J1.1, J1.2
unnamed: D2.2 (A), L2.2
unnamed: D3.1 (KA), R4.2, RN5.1 (R1.1)
unnamed: D4.1 (KA), R7.2, RN5.2 (R2.1)
unnamed: D5.1 (KA), R10.2, RN5.3 (R3.1)
unnamed: D6.1 (KA), R13.2, RN5.4 (R4.1)
unnamed: D7.2 (AK), R15.2, RN13.1 (R1.1)
unnamed: D8.2 (AK), R17.2, RN13.2 (R2.1)
unnamed: D9.2 (AK), R19.2, RN13.3 (R3.1)
unnamed: D10.2 (AK), R21.2, RN13.4 (R4.1)
unnamed: J2.11, J2.12, L3.2
unnamed: J3.T, R2.1
unnamed: J4.T, R5.1
unnamed: J5.T, R8.1
unnamed: J6.T, R11.1
unnamed: J7.T, R14.2
unnamed: J8.T, R16.2
unnamed: J9.T, R18.2
unnamed: J10.T, R20.2
unnamed: RN2.1 (R1.1), RN2.2 (R2.1), U2.3 (+)
unnamed: RN2.3 (R3.1), RN2.4 (R4.1), U2.6 (-)
unnamed: RN2.6 (R3.2), U2.1, U2.2 (-)
unnamed: RN3.5 (R4.2), RN3.6 (R3.2), U4.3 (+)
unnamed: RN4.1 (R1.1), RN4.2 (R2.1), U5.3 (+)
unnamed: RN4.3 (R3.1), RN4.4 (R4.1), U5.5 (+)
unnamed: RN6.5 (R4.2), RN6.6 (R3.2), U4.5 (+)
unnamed: RN7.5 (R4.2), RN7.6 (R3.2), U4.10 (+)
unnamed: RN8.1 (R1.1), RN8.2 (R2.1), U5.10 (+)
unnamed: RN8.3 (R3.1), RN8.4 (R4.1), U5.12 (+)
unnamed: RN9.5 (R4.2), RN9.6 (R3.2), U4.12 (+)
unnamed: RN10.5 (R4.2), RN10.6 (R3.2), U6.5 (+), U7.5 (+)
unnamed: RN10.7 (R2.2), RN10.8 (R1.2), U6.3 (+), U7.3 (+)
unnamed: RN14.5 (R4.2), RN14.6 (R3.2), U6.12 (+), U7.12 (+)
unnamed: RN14.7 (R2.2), RN14.8 (R1.2), U6.10 (+), U7.10 (+)
VDD: C5.1, C6.1, C7.1, L3.1, L4.2, RN1.5 (R4.2), RN1.6 (R3.2), RN1.7 (R2.2), U3.3 (TVDD)

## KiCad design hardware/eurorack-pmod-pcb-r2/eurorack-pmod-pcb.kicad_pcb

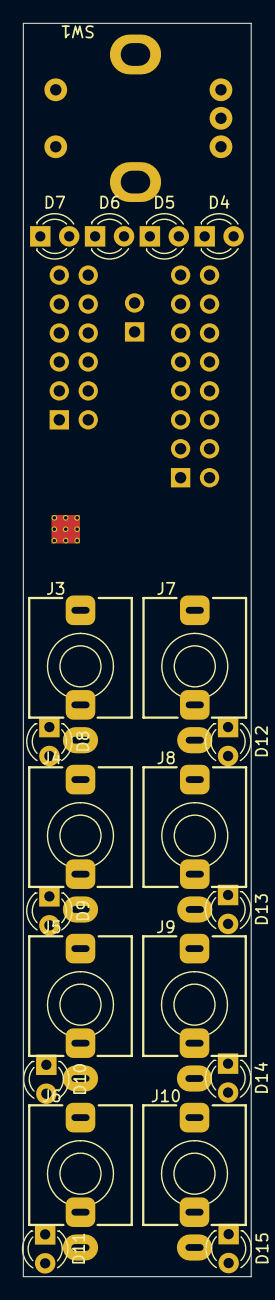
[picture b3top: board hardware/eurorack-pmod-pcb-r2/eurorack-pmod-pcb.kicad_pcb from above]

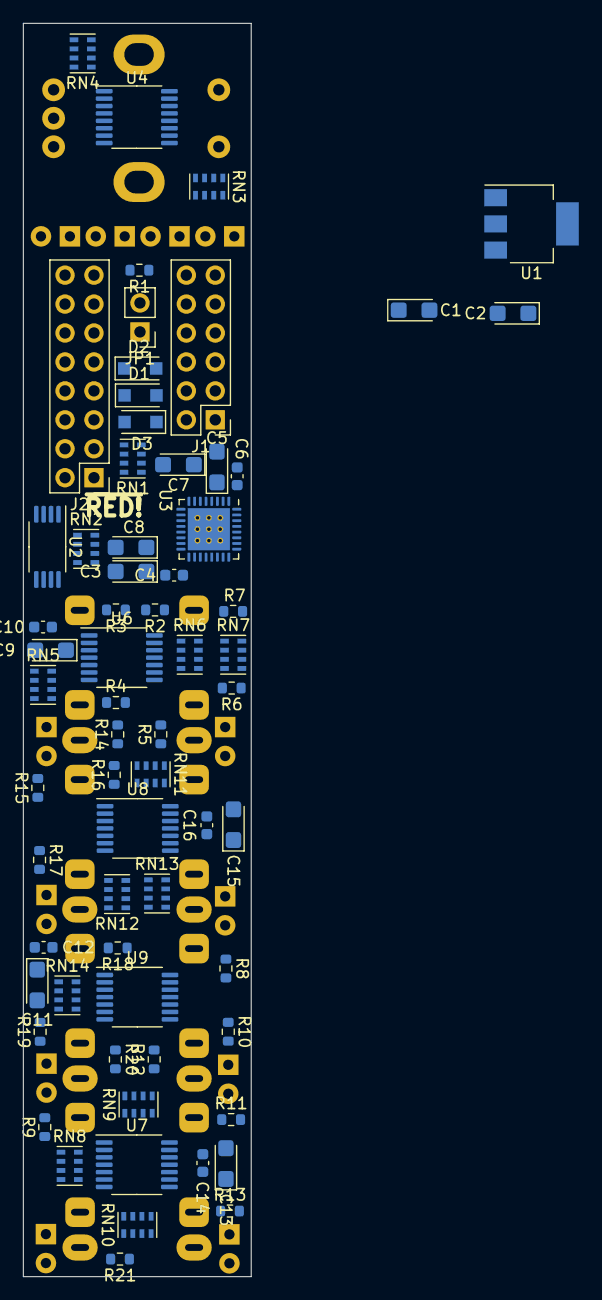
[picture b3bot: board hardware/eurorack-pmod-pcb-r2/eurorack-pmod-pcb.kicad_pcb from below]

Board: 2 copper layers, 20.0 x 110.0 mm, 86 parts (65 on the bottom side), 93 nets, no tracks yet.

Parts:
C1, C2, C3, C5, C9, C11, C13, C15: 10u; CP_EIA-3216-10_Kemet-I
C4, C6, C10, C12, C14, C16: 100n; C_0603_1608Metric
C7, C8: 2u2; CP_EIA-3216-10_Kemet-I
D1, D2, D3: 1N4007FL; D_SOD-123F
D4, D5, D6, D7: LED_UI; LED_D3.0mm_Clear
D8, D9, D10, D11, D12, D13, D14, D15: LED_AN; LED_D3.0mm_Clear
J1: PMOD; PinHeader_2x06_P2.54mm_Vertical
J2: EURORACK_PWR; PinHeader_2x08_P2.54mm_Vertical
J3, J4, J5, J6, J7, J8, J9, J10: PJ398SM; Jack_3.5mm_QingPu_WQP-PJ398SM_Vertical
JP1: JUMPER_3V3; PinHeader_1x02_P2.54mm_Vertical
R1: 0R; R_0603_1608Metric
R2, R5, R8, R11: 100K; R_0603_1608Metric
R3, R6, R9, R12, R14, R16, R18, R20: 1K; R_0603_1608Metric
R4, R7, R10, R13, R15, R17, R19, R21: 100R; R_0603_1608Metric
RN1, RN13: 4K7; R_Cat16-4
RN2, RN6, RN9, RN11, RN14: 100K; R_Cat16-4
RN3: 220R; R_Cat16-4
RN4: 10K; R_Cat16-4
RN5, RN7, RN8, RN10: 15K; R_Cat16-4
RN12: 56K; R_Cat16-4
SW1: PEC12R-3225F-S0024; PEC12R-3220F-S0024
U1: LM1117-3.3; SOT-223-3_TabPin2
U2: TL072; TSSOP-8_4.4x3mm_P0.65mm
U3: AK4619VN; QFN-32-1EP_5x5mm_P0.5mm_EP3.7x3.7mm_ThermalVias
U4: PCA9557DBR; TSSOP-16_4.4x5mm_P0.65mm
U6, U7, U8, U9: TL074; TSSOP-14_4.4x5mm_P0.65mm

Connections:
+3.3VA: C2.1, C3.1, C4.1, JP1.1 (A), RN2.8 (R1.2), U1.2 (VO), U3.18 (AVDD), U3.21 (VREFH)
+5V: C1.1, D2.1 (K), J2.11, J2.12, U1.3 (VI)
+12V: C9.1, C10.1, C11.1, C12.1, D1.1 (K), J2.9, J2.10, U2.8 (V+), U6.4 (V+), U7.4 (V+), U8.4 (V+), U9.4 (V+)
-12V: C13.2, C14.2, C15.2, C16.2, D3.2 (A), J2.1, J2.2, U2.4 (V-), U6.11 (V-), U7.11 (V-), U8.11 (V-), U9.11 (V-)
/-VCOM: RN2.5 (R4.2), RN5.8 (R1.2), RN6.5 (R4.2), RN6.7 (R2.2), RN7.8 (R1.2), RN8.8 (R1.2), RN9.5 (R4.2), RN9.7 (R2.2), RN10.8 (R1.2), RN11.1 (R1.1), RN11.3 (R3.1), RN14.1 (R1.1), RN14.3 (R3.1), U2.7
/BICK: J1.7, U3.7 (BICK)
/ENC_A: RN4.1 (R1.1), SW1.A, U4.7 (IO1)
/ENC_B: RN4.5 (R4.2), SW1.B, U4.9 (IO2)
/ENC_SW: RN4.6 (R3.2), RN4.7 (R2.2), SW1.S2, U4.6 (IO0)
/LRCK: J1.5, U3.6 (LRCK)
/MCLK: J1.8, U3.8 (MCLK)
/PDN: J1.6, RN1.4 (R4.1), U3.26 (PDN), U4.15 (~RESET)
/SCL: J1.2, RN1.2 (R2.1), U3.28 (SCL/SCLK), U4.1 (SCL)
/SDA: J1.4, RN1.3 (R3.1), U3.30 (SDA/SO), U4.2 (SDA)
/SDIN1: J1.1, U3.1 (SDIN1)
/SDOUT1: J1.3, U3.31 (SDOUT1)
/dual_mono_inputs1/IN1_3V: R3.2, U3.16 (IN1P/AIN1L/AIN3L)
/dual_mono_inputs1/IN2_3V: R6.2, U3.14 (IN2P/AIN1R/AIN3R)
/dual_mono_inputs2/IN1_3V: R9.2, U3.12 (IN3P/AIN4L/AIN6L)
/dual_mono_inputs2/IN2_3V: R12.2, U3.10 (IN4P/AIN4R/AIN6R)
/dual_mono_outputs1/OUT1: RN11.2 (R2.1), U3.22 (AOUT1L)
/dual_mono_outputs1/OUT2: RN11.4 (R4.1), U3.23 (AOUT1R)
/dual_mono_outputs2/OUT1: RN14.2 (R2.1), U3.24 (AOUT2L)
/dual_mono_outputs2/OUT2: RN14.4 (R4.1), U3.25 (AOUT2R)
GND: C1.2, C2.2, C3.2, C4.2, C5.2, C6.2, C7.2, C8.2, C9.2, C10.2, C11.2, C12.2, C13.1, C14.1, C15.1, C16.1, D1.2 (A), D2.2 (A), D3.1 (K), J1.9, J1.10, J2.3, J2.4, J2.5, J2.6, J2.7, J2.8, J3.S, J3.TN, J4.S, J4.TN, J5.S, J5.TN, J6.S, J6.TN, J7.S, J7.TN, J8.S, J8.TN, J9.S, J9.TN, J10.S, J10.TN, R4.1, R7.1, R10.1, R13.1, R15.1, R17.1, R19.1, R21.1, RN2.7 (R2.2), RN5.3 (R3.1), RN5.4 (R4.1), RN7.3 (R3.1), RN7.4 (R4.1), RN8.3 (R3.1), RN8.4 (R4.1), RN10.3 (R3.1), RN10.4 (R4.1), RN13.5 (R4.2), RN13.6 (R3.2), RN13.7 (R2.2), RN13.8 (R1.2), SW1.C, SW1.S1, U1.1 (GND), U2.5 (+), U3.2 (SDIN2), U3.4 (VSS2), U3.19 (VSS1), U3.20 (VREFL), U3.27 (CAD/~CS), U3.29 (SI), U3.33 (PAD), U4.3 (A0), U4.4 (A1), U4.5 (A2)
unnamed: C7.1, U3.5 (AVDRV)
unnamed: C8.1, U3.17 (VCOM)
unnamed: D4.1 (KA), RN3.6 (R3.2)
unnamed: D4.2 (AK), D5.2 (AK), D6.2 (AK), D7.2 (AK), U4.14 (IO7)
unnamed: D5.1 (KA), RN3.5 (R4.2)
unnamed: D6.1 (KA), RN3.7 (R2.2)
unnamed: D7.1 (KA), RN3.8 (R1.2)
unnamed: D8.1 (KA), R4.2, U6.6 (-)
unnamed: D8.2 (AK), U6.7
unnamed: D9.1 (KA), R7.2, U6.13 (-)
unnamed: D9.2 (AK), U6.14
unnamed: D10.1 (KA), R10.2, U7.6 (-)
unnamed: D10.2 (AK), U7.7
unnamed: D11.1 (KA), R13.2, U7.13 (-)
unnamed: D11.2 (AK), U7.14
unnamed: D12.1 (KA), U8.7
unnamed: D12.2 (AK), R15.2, U8.6 (-)
unnamed: D13.1 (KA), U8.14
unnamed: D13.2 (AK), R17.2, U8.13 (-)
unnamed: D14.1 (KA), U9.7
unnamed: D14.2 (AK), R19.2, U9.6 (-)
unnamed: D15.1 (KA), U9.14
unnamed: D15.2 (AK), R21.2, U9.13 (-)
unnamed: J1.11, J1.12, R1.1
unnamed: J3.T, R2.1
unnamed: J4.T, R5.1
unnamed: J5.T, R8.1
unnamed: J6.T, R11.1
unnamed: J7.T, R14.2
unnamed: J8.T, R16.2
unnamed: J9.T, R18.2
unnamed: J10.T, R20.2
unnamed: R2.2, RN5.1 (R1.1), RN5.2 (R2.1), U6.2 (-)
unnamed: R3.1, RN5.7 (R2.2), RN6.8 (R1.2), U6.1
unnamed: R5.2, RN7.1 (R1.1), RN7.2 (R2.1), U6.10 (+)
unnamed: R6.1, RN6.6 (R3.2), RN7.7 (R2.2), U6.8
unnamed: R8.2, RN8.1 (R1.1), RN8.2 (R2.1), U7.2 (-)
unnamed: R9.1, RN8.7 (R2.2), RN9.8 (R1.2), U7.1
unnamed: R11.2, RN10.1 (R1.1), RN10.2 (R2.1), U7.10 (+)
unnamed: R12.1, RN9.6 (R3.2), RN10.7 (R2.2), U7.8
unnamed: R14.1, RN12.8 (R1.2), U8.1
unnamed: R16.1, RN12.7 (R2.2), U8.8
unnamed: R18.1, RN12.6 (R3.2), U9.1
unnamed: R20.1, RN12.5 (R4.2), U9.8
unnamed: RN2.1 (R1.1), RN2.2 (R2.1), U2.3 (+)
unnamed: RN2.3 (R3.1), RN2.4 (R4.1), U2.6 (-)
unnamed: RN2.6 (R3.2), U2.1, U2.2 (-)
unnamed: RN3.1 (R1.1), U4.10 (IO3)
unnamed: RN3.2 (R2.1), U4.11 (IO4)
unnamed: RN3.3 (R3.1), U4.13 (IO6)
unnamed: RN3.4 (R4.1), U4.12 (IO5)
unnamed: RN5.5 (R4.2), RN5.6 (R3.2), U6.3 (+)
unnamed: RN6.1 (R1.1), RN6.2 (R2.1), U6.5 (+)
unnamed: RN6.3 (R3.1), RN6.4 (R4.1), U6.12 (+)
unnamed: RN7.5 (R4.2), RN7.6 (R3.2), U6.9 (-)
unnamed: RN8.5 (R4.2), RN8.6 (R3.2), U7.3 (+)
unnamed: RN9.1 (R1.1), RN9.2 (R2.1), U7.5 (+)
unnamed: RN9.3 (R3.1), RN9.4 (R4.1), U7.12 (+)
unnamed: RN10.5 (R4.2), RN10.6 (R3.2), U7.9 (-)
unnamed: RN11.5 (R4.2), RN11.6 (R3.2), U8.10 (+), U8.12 (+)
unnamed: RN11.7 (R2.2), RN11.8 (R1.2), U8.3 (+), U8.5 (+)
unnamed: RN12.1 (R1.1), RN13.1 (R1.1), U8.2 (-)
unnamed: RN12.2 (R2.1), RN13.2 (R2.1), U8.9 (-)
unnamed: RN12.3 (R3.1), RN13.3 (R3.1), U9.2 (-)
unnamed: RN12.4 (R4.1), RN13.4 (R4.1), U9.9 (-)
unnamed: RN14.5 (R4.2), RN14.6 (R3.2), U9.10 (+), U9.12 (+)
unnamed: RN14.7 (R2.2), RN14.8 (R1.2), U9.3 (+), U9.5 (+)
VDD: C5.1, C6.1, JP1.2 (B), R1.2, RN1.5 (R4.2), RN1.6 (R3.2), RN1.7 (R2.2), RN4.2 (R2.1), RN4.3 (R3.1), RN4.4 (R4.1), RN4.8 (R1.2), U3.3 (TVDD), U4.16 (VDD)

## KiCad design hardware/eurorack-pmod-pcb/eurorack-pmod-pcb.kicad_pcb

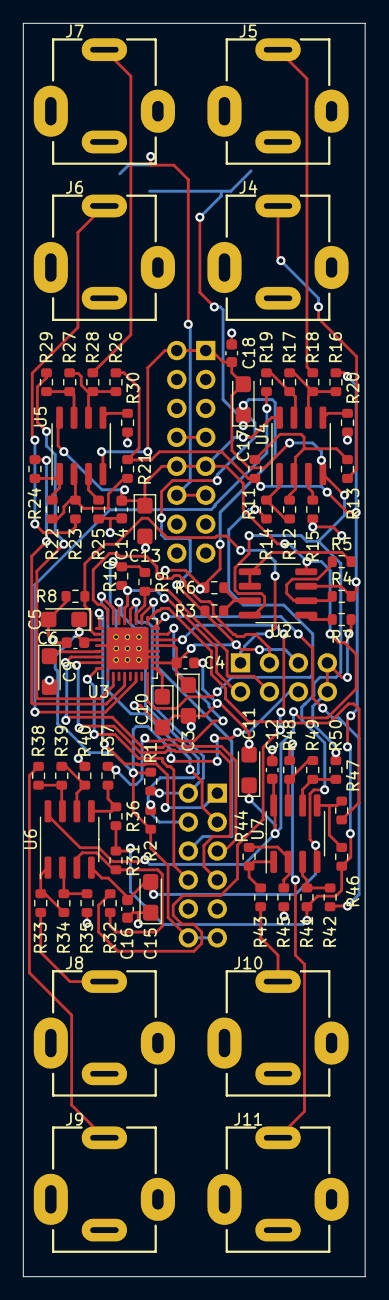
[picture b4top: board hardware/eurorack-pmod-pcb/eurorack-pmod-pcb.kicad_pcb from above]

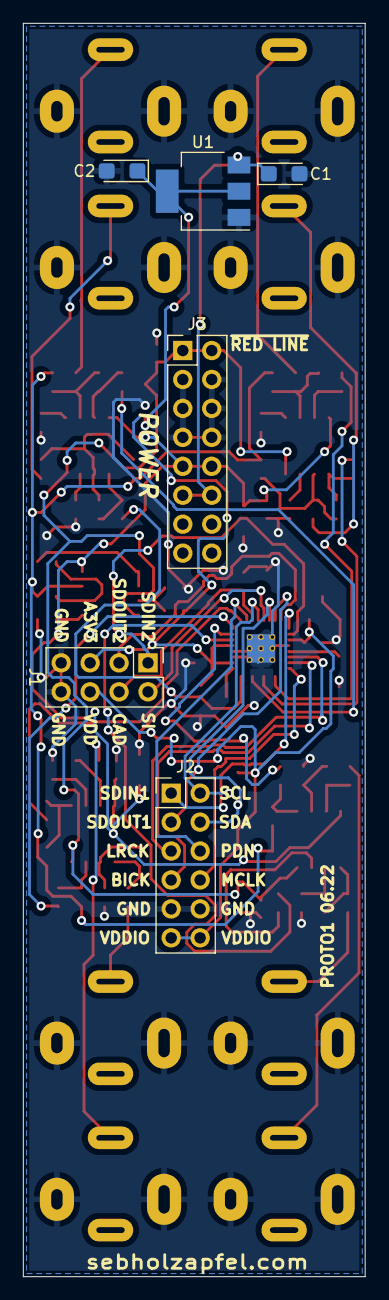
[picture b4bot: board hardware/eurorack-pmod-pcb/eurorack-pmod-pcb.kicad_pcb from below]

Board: 2 copper layers, 30.0 x 110.0 mm, 84 parts (6 on the bottom side), 65 nets.

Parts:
C1, C2, C3, C5, C11, C13, C15, C17: 10u; CP_EIA-3216-10_Kemet-I
C4, C6, C12, C14, C16, C18: 100n; C_0603_1608Metric
C9, C10: 2u2; CP_EIA-3216-10_Kemet-I
J1: OPTIONAL; PinHeader_2x04_P2.54mm_Vertical
J2: PMOD; PinHeader_2x06_P2.54mm_Vertical
J3: EURORACK_PWR; PinHeader_2x08_P2.54mm_Vertical
J4, J5, J6, J7, J8, J9, J10, J11: PJ301BM; Jack_3.5mm_QingPu_WQP-PJ301BM_Vertical
R1, R2, R4, R5, R8, R9, R10, R35, R40, R45, R50: 4K7; R_0603_1608Metric
R3, R6, R13, R18, R23, R28, R31, R32, R36, R37, R41, R42, R46, R47: 100K; R_0603_1608Metric
R7: 2K2; R_0603_1608Metric
R11, R12, R16, R17, R21, R22, R26, R27: 15K; R_0603_1608Metric
R14, R19, R24, R29, R33, R38, R43, R48: 1K; R_0603_1608Metric
R15, R20, R25, R30: 8K2; R_0603_1608Metric
R34, R39, R44, R49: 56K; R_0603_1608Metric
U1: LM1117-3.3; SOT-223-3_TabPin2
U2, U4, U5, U6, U7: TL072; SOIC-8_3.9x4.9mm_P1.27mm
U3: AK4619VN; QFN-32-1EP_5x5mm_P0.5mm_EP3.7x3.7mm_ThermalVias

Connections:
+3.3VA: C2.1, C3.1, C4.1, J1.5, R3.1, U1.2 (VO), U3.18 (AVDD), U3.21 (VREFH)
+5V: C1.1, J3.11, J3.12, U1.3 (VI)
+12V: C11.1, C12.1, C13.1, C14.1, J3.9, J3.10, U2.8 (V+), U4.8 (V+), U5.8 (V+), U6.8 (V+), U7.8 (V+)
-12V: C15.2, C16.2, C17.2, C18.2, J3.1, J3.2, U2.4 (V-), U4.4 (V-), U5.4 (V-), U6.4 (V-), U7.4 (V-)
/-VCOM: R4.2, R11.1, R16.1, R21.1, R26.1, R31.1, R36.1, R41.1, R46.1, U2.7
/BICK: J2.7, U3.7 (BICK)
/CAD/~CS: J1.4, R9.1, U3.27 (CAD/~CS)
/LRCK: J2.5, U3.6 (LRCK)
/MCLK: J2.8, U3.8 (MCLK)
/PDN: J2.6, U3.26 (PDN)
/SCL: J2.2, R1.2, U3.28 (SCL/SCLK)
/SDA: J2.4, R2.2, U3.30 (SDA/SO)
/SDIN1: J2.1, U3.1 (SDIN1)
/SDIN2: J1.1, R8.1, U3.2 (SDIN2)
/SDOUT1: J2.3, U3.31 (SDOUT1)
/SDOUT2: J1.3, U3.32 (SDOUT2)
/SI: J1.2, R10.1, U3.29 (SI)
/dual_mono_inputs1/IN1_3V: R14.2, U3.16 (IN1P/AIN1L/AIN3L)
/dual_mono_inputs1/IN2_3V: R19.2, U3.14 (IN2P/AIN1R/AIN3R)
/dual_mono_inputs2/IN1_3V: R24.2, U3.12 (IN3P/AIN4L/AIN6L)
/dual_mono_inputs2/IN2_3V: R29.2, U3.10 (IN4P/AIN4R/AIN6R)
/dual_mono_outputs1/OUT1: R32.1, U3.22 (AOUT1L)
/dual_mono_outputs1/OUT2: R37.1, U3.23 (AOUT1R)
/dual_mono_outputs2/OUT1: R42.1, U3.24 (AOUT2L)
/dual_mono_outputs2/OUT2: R47.1, U3.25 (AOUT2R)
GND: C1.2, C2.2, C3.2, C4.2, C5.2, C6.2, C9.2, C10.2, C11.2, C12.2, C13.2, C14.2, C15.1, C16.1, C17.1, C18.1, J1.7, J1.8, J2.9, J2.10, J3.3, J3.4, J3.5, J3.6, J3.7, J3.8, J4.S, J5.S, J6.S, J7.S, J8.S, J9.S, J10.S, J11.S, R6.2, R7.2, R8.2, R9.2, R10.2, R15.2, R20.2, R25.2, R30.2, R35.2, R40.2, R45.2, R50.2, U1.1 (GND), U3.4 (VSS2), U3.19 (VSS1), U3.20 (VREFL), U3.33 (PAD)
unnamed: C9.1, U3.5 (AVDRV)
unnamed: C10.1, U3.17 (VCOM)
unnamed: J4.T, R13.1
unnamed: J5.T, R18.1
unnamed: J6.T, R23.1
unnamed: J7.T, R28.1
unnamed: J8.T, R33.2
unnamed: J9.T, R38.2
unnamed: J10.T, R43.2
unnamed: J11.T, R48.2
unnamed: R3.2, R6.1, U2.3 (+)
unnamed: R4.1, R5.2, U2.6 (-)
unnamed: R5.1, U2.1, U2.2 (-)
unnamed: R7.1, U2.5 (+)
unnamed: R11.2, R12.1, R13.2, U4.2 (-)
unnamed: R12.2, R14.1, U4.1
unnamed: R15.1, U4.3 (+)
unnamed: R16.2, R17.1, R18.2, U4.6 (-)
unnamed: R17.2, R19.1, U4.7
unnamed: R20.1, U4.5 (+)
unnamed: R21.2, R22.1, R23.2, U5.2 (-)
unnamed: R22.2, R24.1, U5.1
unnamed: R25.1, U5.3 (+)
unnamed: R26.2, R27.1, R28.2, U5.6 (-)
unnamed: R27.2, R29.1, U5.7
unnamed: R30.1, U5.5 (+)
unnamed: R31.2, R32.2, U6.3 (+)
unnamed: R33.1, R34.2, U6.1
unnamed: R34.1, R35.1, U6.2 (-)
unnamed: R36.2, R37.2, U6.5 (+)
unnamed: R38.1, R39.2, U6.7
unnamed: R39.1, R40.1, U6.6 (-)
unnamed: R41.2, R42.2, U7.3 (+)
unnamed: R43.1, R44.2, U7.1
unnamed: R44.1, R45.1, U7.2 (-)
unnamed: R46.2, R47.2, U7.5 (+)
unnamed: R48.1, R49.2, U7.7
unnamed: R49.1, R50.1, U7.6 (-)
VDD: C5.1, C6.1, J1.6, J2.11, J2.12, R1.1, R2.1, U3.3 (TVDD)

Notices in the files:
hardware/eurorack-pmod-pcb-flat/eurorack-pmod-pcb.kicad_pcb:
CC-BY-SA 4.0
hardware/eurorack-pmod-r3.3/eurorack-pmod-pcb.kicad_pcb:
CERN-OHL-S V2
